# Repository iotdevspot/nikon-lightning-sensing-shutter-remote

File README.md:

# nikon-lightning-sensing-shutter-remote
This project is an implemenation of the following shutter remote: [http://fototipp.hu/light2](http://fototipp.hu/light2)

## How to deploy:

I've programmed the MCU with the .HEX file separately via pickit3, but I've added programming connector to the schematics. It's your choice how to upload the code. The board design is created by Eagle and the gerber files available too. I've created an enclosure for it but it should be refactored before I publish it because there are some issues to fix.

## How to use:

There are two phases of using this shutter remote. The first one is the setting of the sensitivity. In this mode the red and blue LEDs blink one after another. After the LEDs turn off the second phase is active. In this phase we have to adjust the sensitivity of the sensor with the potentiometer. If the blue LED lights the sensitivity is there is too much light and if the red LED lights then there is too few light. The sweet spot is where the blue LED just lights up so where we are a bit over the edge where the red changes to blue. After this we can start the remote by the pushing the button and the yellow LED lights up. This indicates the focus signal is active and the remainging green LED is for indicating the exposure. To adjoust the sensitivity on the potentiometer clockwise turn decreases and counterclockwise turn will increase the sensitivity

Peolpe in the blog's comment section claimed it works fine. I need more tests to determine wether it works well or not. My indoor tests resulted that it needs quite a bigger impulse to trigger, but probably this was the aim by the creator.

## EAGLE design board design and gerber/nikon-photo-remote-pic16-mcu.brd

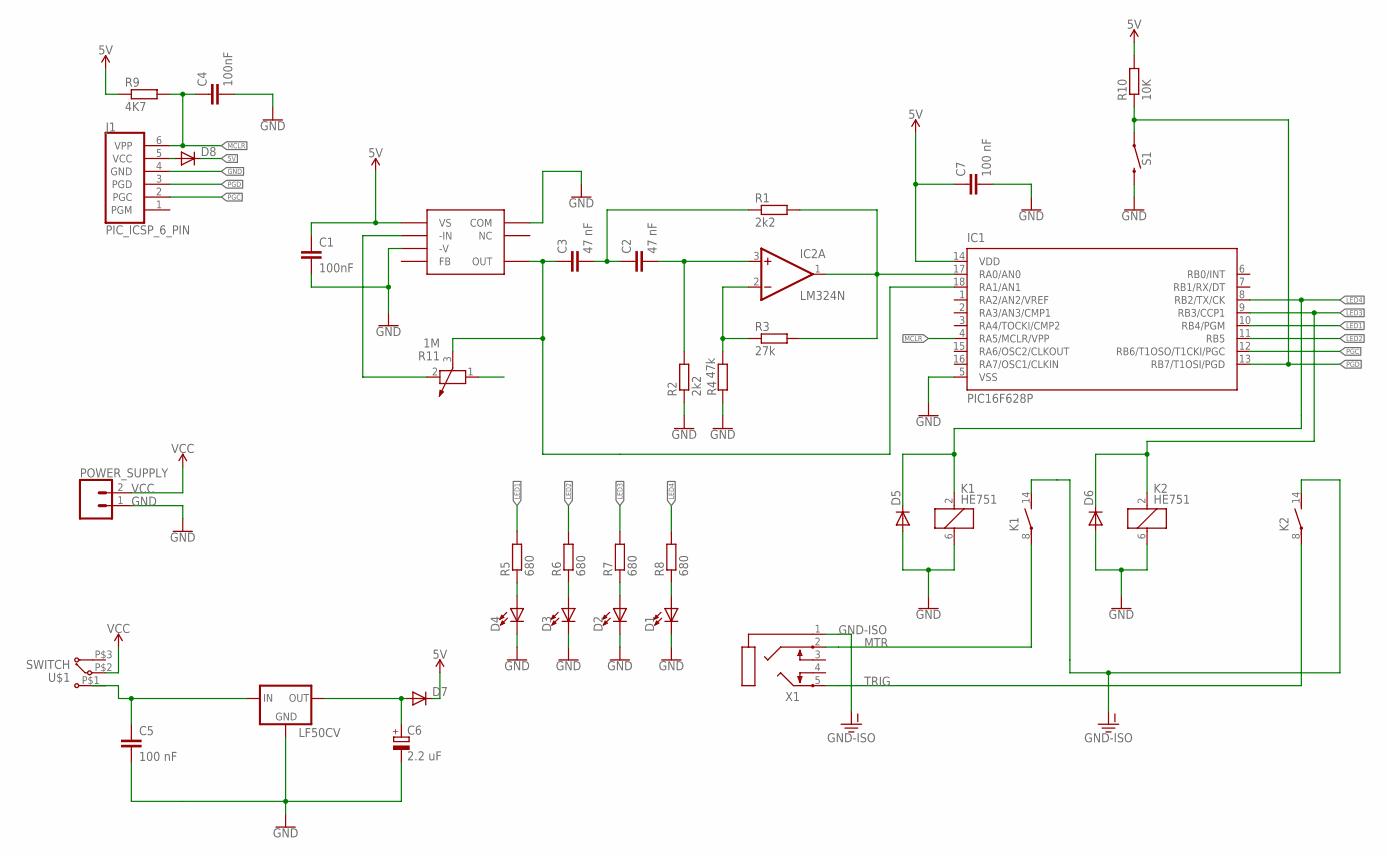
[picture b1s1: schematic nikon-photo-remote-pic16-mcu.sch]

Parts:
C1, C4: 100nF; C025-024X044
C2, C3: 47 nF; C025-024X044
C5, C7: 100 nF; C025-024X044
C6: 2.2 uF; E2,5-6
D1, D2, D3, D4: LED5MM; LED5MM_CLEAR
D5, D6: DIODED-10; D-10
D7, D8: DIODED-7.5; D-7.5
IC1: PIC16F628P; DIL18
IC2: LM324N; DIL14
J1: PIC_ICSP_6_PIN; MOLEX-1X6
K1, K2: HE751
LF50CV: V_REG_78XX_LAYING; 78XXL
OPT101: OPT101; DIL08
POWER_SUPPLY: CONN_02; 1X02_S
R1, R2: 2k2; 0207/7
R3: 27k; 0207/7
R4: 47k; 0207/7
R5, R6, R7, R8: 680; 0207/7
R9: 4K7; 0207/7
R10: 10K; 0204V
R11: 1M; POT_ALPHA_RV16AF-20
S1: INPUT_MOMENTARY_SWITCH_SPST-PTH-6.0MM; TACTILE_SWITCH_PTH_6.0MM
U$1: SWITCH
X1: CONN_JACK_3.5MM_PG203J; PG203J

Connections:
5V: C1.1, C7.1, D7.C, D8.C, IC1.14 (VDD), OPT101.1 (VS), R9.1, R10.2
GND: C1.2, C4.2, C5.2, C6.-, C7.2, D1.K (C), D2.K (C), D3.K (C), D4.K (C), D5.A, D6.A, IC1.5 (VSS), J1.4 (GND), K1.6 (2), K2.6 (2), LF50CV.GND, OPT101.3 (-V), OPT101.8 (COM), POWER_SUPPLY.1, R2.1, R4.2, S1.3 (2)
GND-ISO: K1.14 (S), K2.14 (S), X1.1
LED1: IC1.10 (RB4/PGM), R5.2
LED2: IC1.11 (RB5), R6.2
LED3: D6.C, IC1.9 (RB3/CCP1), K2.2 (1), R7.2
LED4: D5.C, IC1.8 (RB2/TX/CK), K1.2 (1), R8.2
MCLR: C4.1, IC1.4 (RA5/MCLR/VPP), J1.6 (VPP), R9.2
MTR: K1.8, X1.2
unnamed: C6.+, D7.A, LF50CV.OUT
unnamed: D8.A, J1.5 (VCC)
unnamed: D4.A, R5.1
unnamed: D3.A, R6.1
unnamed: D2.A, R7.1
unnamed: D1.A, R8.1
unnamed: C5.1, LF50CV.IN, U$1.P$1 (1)
unnamed: IC1.17 (RA0/AN0), IC2.1 (OUT), R1.2, R3.2
unnamed: IC2.2 (-IN), R3.1, R4.1
unnamed: C2.2, IC2.3 (+IN), R2.2
unnamed: C2.1, C3.2, R1.1
unnamed: C3.1, IC1.18 (RA1/AN1), OPT101.5 (OUT), R11.3
unnamed: OPT101.2 (-IN), R11.2
PGC: IC1.12 (RB6/T1OSO/T1CKI/PGC), J1.2 (PGC)
PGD: IC1.13 (RB7/T1OSI/PGD), J1.3 (PGD), R10.1, S1.1
TRIG: K2.8, X1.5
V+: IC2.4 (V+)
V-: IC2.11 (V-)
VCC: POWER_SUPPLY.2, U$1.P$2 (2)

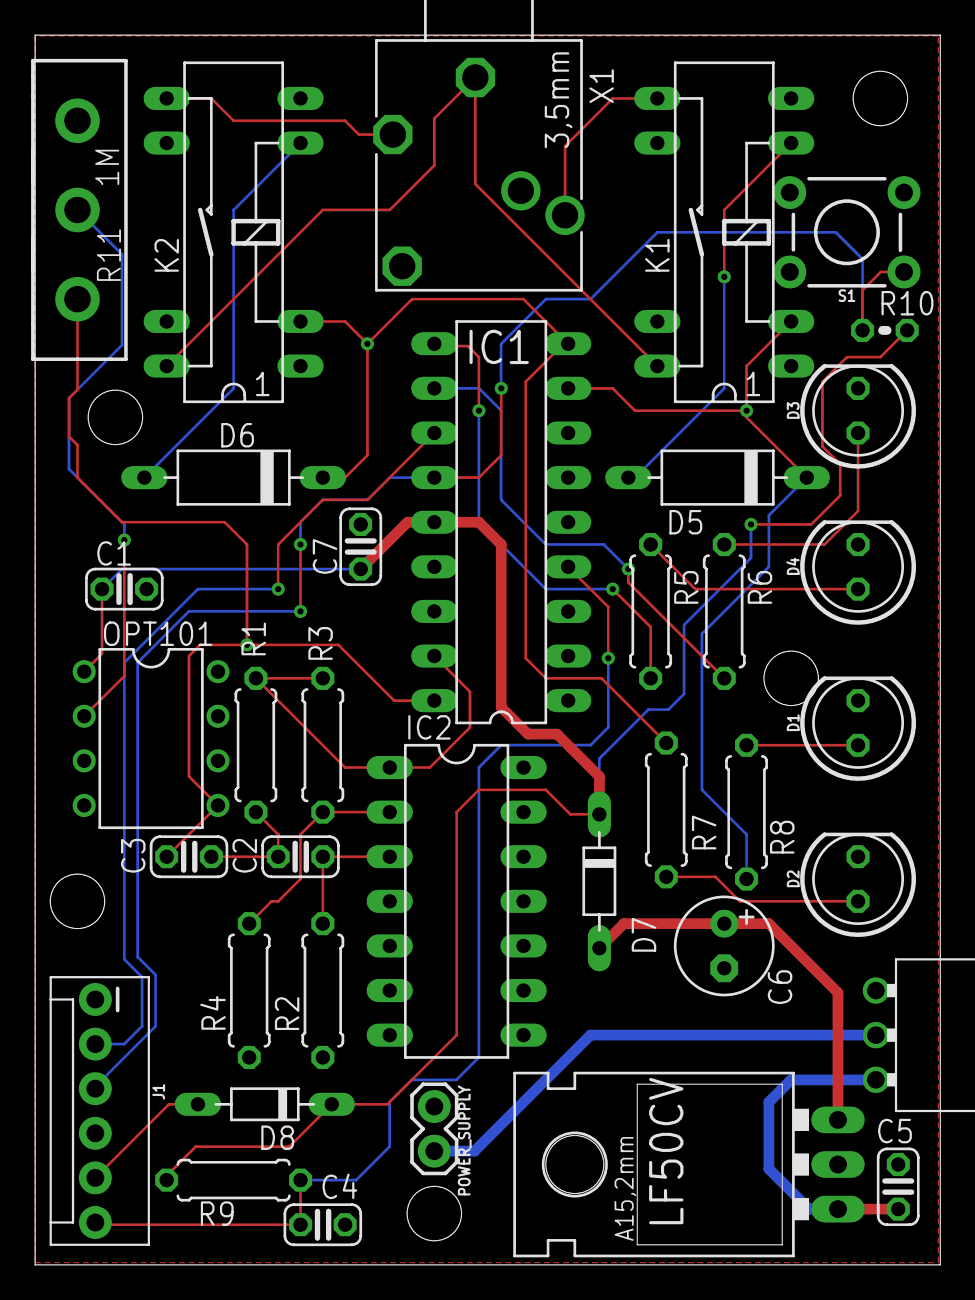
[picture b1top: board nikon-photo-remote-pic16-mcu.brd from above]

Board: 2 copper layers, 51.5 x 70.0 mm, 37 parts (0 on the bottom side), 26 nets.

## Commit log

2018-10-27 Schematics, boardgerbers, code, images added
2018-10-27 Renamed image files

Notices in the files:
parts and their libraries:
SparkFun-Connectors: Licensing: Creative Commons ShareAlike 4.0 International - https://creativecommons.org/licenses/by-sa/4.0
